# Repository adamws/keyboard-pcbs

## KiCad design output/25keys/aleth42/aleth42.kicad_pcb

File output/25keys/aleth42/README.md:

## 25keys/aleth42

[layout](aleth42-kle.json) - [PCB](aleth42.kicad_pcb)

{:loading="lazy"}

[Open in keyboard-layout-editor](http://www.keyboard-layout-editor.com/##@@_c=#777777;&=0,0&_c=#cccccc;&=0,1&=0,2&=0,3&=0,4&=0,5&=0,6&=0,7&=0,8&=0,9&=0,10&_c=#aaaaaa;&=3,10;&@_w:1.25;&=1,0&_c=#cccccc;&=1,1&=1,2&=1,3&=1,4&=1,5&=1,6&=1,7&=1,8&=1,9&_c=#777777&w:1.75;&=1,10;&@_c=#aaaaaa&w:1.75;&=2,0&_c=#cccccc;&=2,1&=2,2&=2,3&=2,4&=2,5&=2,6&=2,7&=2,8&=2,9&_c=#aaaaaa&w:1.25;&=2,10;&@=3,0&_w:1.25;&=3,1&_w:1.25;&=3,2&_w:2.75;&=3,3&_w:2.25;&=3,4&_w:1.25;&=3,5&_w:1.25;&=3,6&=3,7)

{:loading="lazy"}

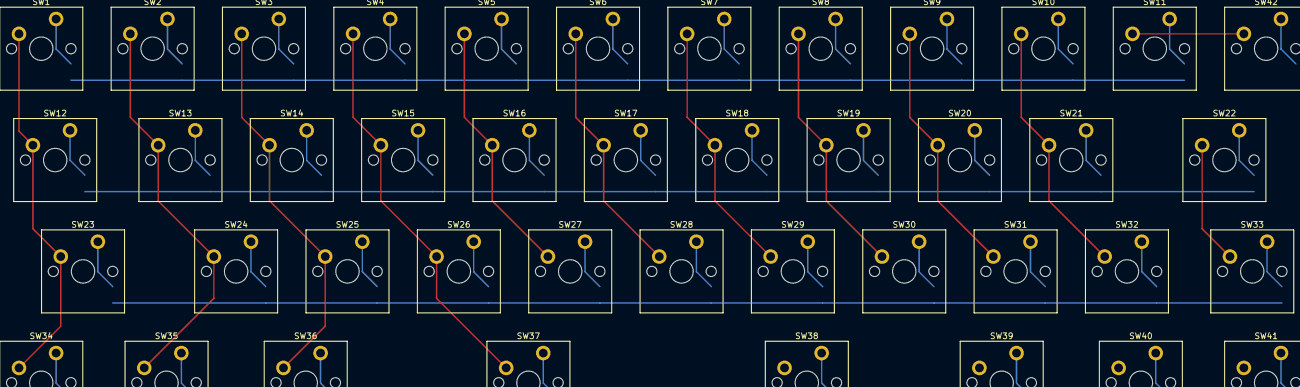
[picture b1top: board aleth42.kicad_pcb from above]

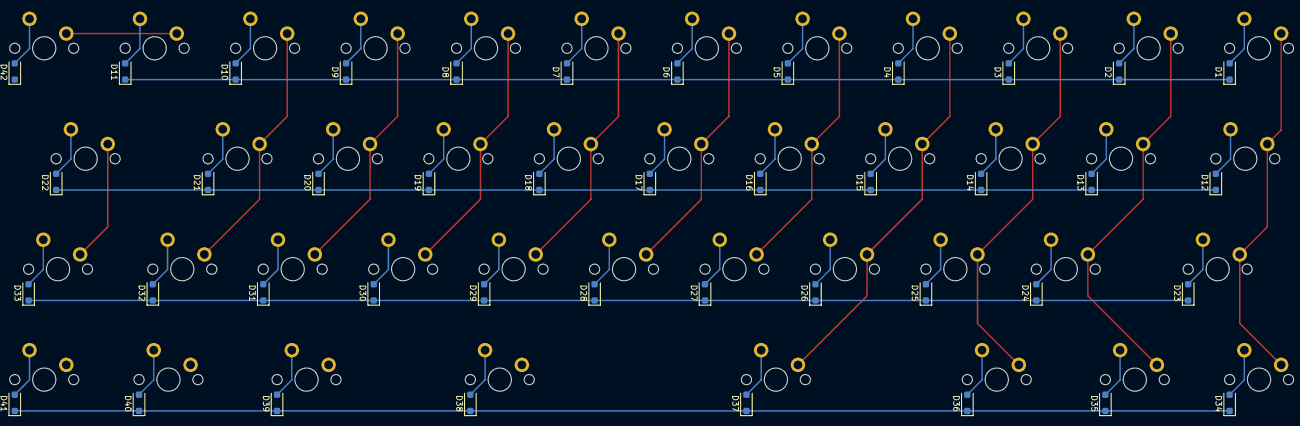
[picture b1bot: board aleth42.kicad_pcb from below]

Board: 2 copper layers, 84 parts (42 on the bottom side), 57 nets.

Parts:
D1, D2, D3, D4, D5, D6, D7, D8, D9, D10, D11, D12, D13, D14, D15, D16, D17, D18, D19, D20, D21, D22, D23, D24, D25, D26, D27, D28, D29, D30, D31, D32, D33, D34, D35, D36, D37, D38, D39, D40, D41, D42: D_SOD-123F
SW1, SW2, SW3, SW4, SW5, SW6, SW7, SW8, SW9, SW10, SW11, SW12, SW13, SW14, SW15, SW16, SW17, SW18, SW19, SW20, SW21, SW22, SW23, SW24, SW25, SW26, SW27, SW28, SW29, SW30, SW31, SW32, SW33, SW34, SW35, SW36, SW37, SW38, SW39, SW40, SW41, SW42: SW_Cherry_MX_PCB_1.00u

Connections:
COL0: SW1.1, SW12.1, SW23.1, SW34.1
COL1: SW2.1, SW13.1, SW24.1, SW35.1
COL2: SW3.1, SW14.1, SW25.1, SW36.1
COL3: SW4.1, SW15.1, SW26.1, SW37.1
COL4: SW5.1, SW16.1, SW27.1, SW38.1
COL5: SW6.1, SW17.1, SW28.1, SW39.1
COL6: SW7.1, SW18.1, SW29.1, SW40.1
COL7: SW8.1, SW19.1, SW30.1, SW41.1
COL8: SW9.1, SW20.1, SW31.1
COL9: SW10.1, SW21.1, SW32.1
COL10: SW11.1, SW22.1, SW33.1, SW42.1
unnamed: D1.2, SW1.2
unnamed: D2.2, SW2.2
unnamed: D3.2, SW3.2
unnamed: D4.2, SW4.2
unnamed: D5.2, SW5.2
unnamed: D6.2, SW6.2
unnamed: D7.2, SW7.2
unnamed: D8.2, SW8.2
unnamed: D9.2, SW9.2
unnamed: D10.2, SW10.2
unnamed: D11.2, SW11.2
unnamed: D12.2, SW12.2
unnamed: D13.2, SW13.2
unnamed: D14.2, SW14.2
unnamed: D15.2, SW15.2
unnamed: D16.2, SW16.2
unnamed: D17.2, SW17.2
unnamed: D18.2, SW18.2
unnamed: D19.2, SW19.2
unnamed: D20.2, SW20.2
unnamed: D21.2, SW21.2
unnamed: D22.2, SW22.2
unnamed: D23.2, SW23.2
unnamed: D24.2, SW24.2
unnamed: D25.2, SW25.2
unnamed: D26.2, SW26.2
unnamed: D27.2, SW27.2
unnamed: D28.2, SW28.2
unnamed: D29.2, SW29.2
unnamed: D30.2, SW30.2
unnamed: D31.2, SW31.2
unnamed: D32.2, SW32.2
unnamed: D33.2, SW33.2
unnamed: D34.2, SW34.2
unnamed: D35.2, SW35.2
unnamed: D36.2, SW36.2
unnamed: D37.2, SW37.2
unnamed: D38.2, SW38.2
unnamed: D39.2, SW39.2
unnamed: D40.2, SW40.2
unnamed: D41.2, SW41.2
unnamed: D42.2, SW42.2
ROW0: D1.1, D2.1, D3.1, D4.1, D5.1, D6.1, D7.1, D8.1, D9.1, D10.1, D11.1
ROW1: D12.1, D13.1, D14.1, D15.1, D16.1, D17.1, D18.1, D19.1, D20.1, D21.1, D22.1
ROW2: D23.1, D24.1, D25.1, D26.1, D27.1, D28.1, D29.1, D30.1, D31.1, D32.1, D33.1
ROW3: D34.1, D35.1, D36.1, D37.1, D38.1, D39.1, D40.1, D41.1, D42.1

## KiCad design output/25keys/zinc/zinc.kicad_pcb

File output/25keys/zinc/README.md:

## 25keys/zinc

[layout](zinc-kle.json) - [PCB](zinc.kicad_pcb)

{:loading="lazy"}

[Open in keyboard-layout-editor](http://www.keyboard-layout-editor.com/##@@_x:0.75&c=#aaaaaa;&=0,0%0A%0A%0A0,0&_c=#cccccc;&=0,1%0A%0A%0A0,0&=0,2%0A%0A%0A0,0&=0,3%0A%0A%0A0,0&=0,4%0A%0A%0A0,0&=0,5%0A%0A%0A0,0&_x:1.75;&=4,0&=4,1&=4,2&=4,3&=4,4&_c=#aaaaaa;&=4,5;&@_x:1;&=1,0%0A%0A%0A0,0&_c=#cccccc;&=1,1%0A%0A%0A0,0&=1,2%0A%0A%0A0,0&=1,3%0A%0A%0A0,0&=1,4%0A%0A%0A0,0&=1,5%0A%0A%0A0,0&_x:1.75;&=5,0&=5,1&=5,2&=5,3&=5,4&=5,5;&@_x:1.25&c=#aaaaaa;&=2,0%0A%0A%0A0,0&_c=#cccccc;&=2,1%0A%0A%0A0,0&=2,2%0A%0A%0A0,0&=2,3%0A%0A%0A0,0&=2,4%0A%0A%0A0,0&=2,5%0A%0A%0A0,0&_x:1.75;&=6,0&=6,1&=6,2&=6,3&=6,4&_c=#aaaaaa;&=6,5;&@_x:1.5;&=3,0%0A%0A%0A0,0&=3,1%0A%0A%0A0,0&=3,2%0A%0A%0A0,0&=3,3%0A%0A%0A0,0&=3,4%0A%0A%0A0,0&_c=#cccccc;&=3,5%0A%0A%0A0,0&_x:1.75;&=7,0&_c=#aaaaaa;&=7,1&=7,2&=7,3&=7,4&=7,5;&@_x:2.25&y:0.5;&=0,0%0A%0A%0A0,1&_c=#cccccc;&=0,1%0A%0A%0A0,1&=0,2%0A%0A%0A0,1&=0,3%0A%0A%0A0,1&=0,4%0A%0A%0A0,1&=0,5%0A%0A%0A0,1;&@_x:2&c=#aaaaaa;&=1,0%0A%0A%0A0,1&_c=#cccccc;&=1,1%0A%0A%0A0,1&=1,2%0A%0A%0A0,1&=1,3%0A%0A%0A0,1&=1,4%0A%0A%0A0,1&=1,5%0A%0A%0A0,1;&@_x:1.75&c=#aaaaaa;&=2,0%0A%0A%0A0,1&_c=#cccccc;&=2,1%0A%0A%0A0,1&=2,2%0A%0A%0A0,1&=2,3%0A%0A%0A0,1&=2,4%0A%0A%0A0,1&=2,5%0A%0A%0A0,1;&@_x:1.5&c=#aaaaaa;&=3,0%0A%0A%0A0,1&=3,1%0A%0A%0A0,1&=3,2%0A%0A%0A0,1&=3,3%0A%0A%0A0,1&=3,4%0A%0A%0A0,1&_c=#cccccc;&=3,5%0A%0A%0A0,1)

{:loading="lazy"}

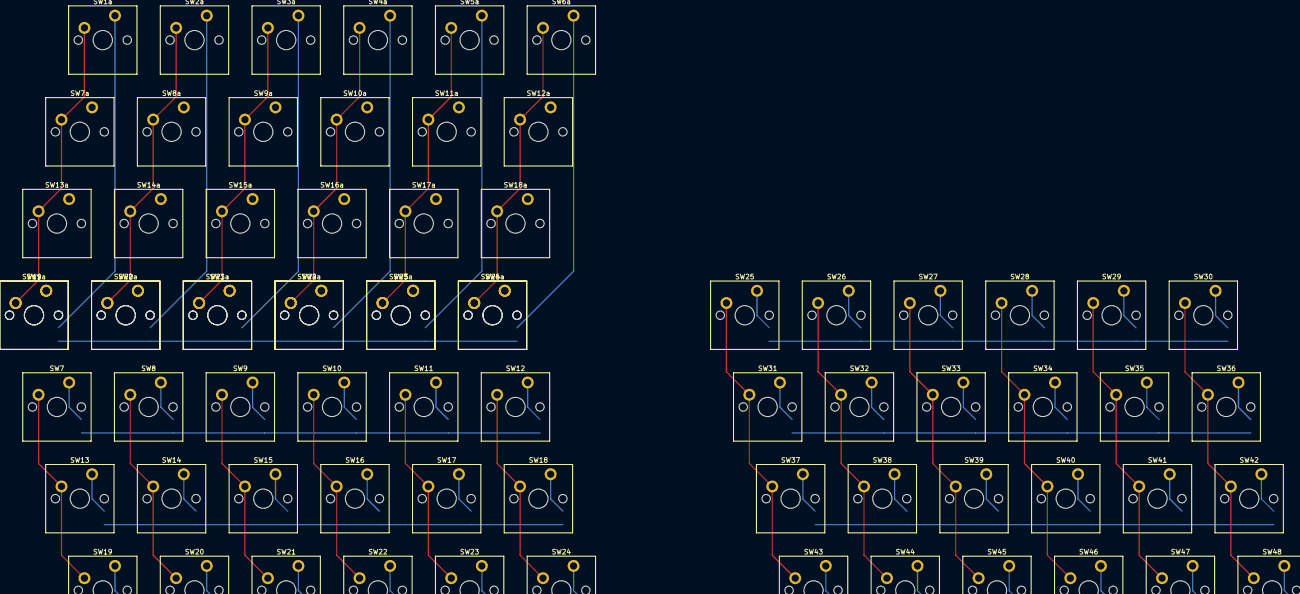
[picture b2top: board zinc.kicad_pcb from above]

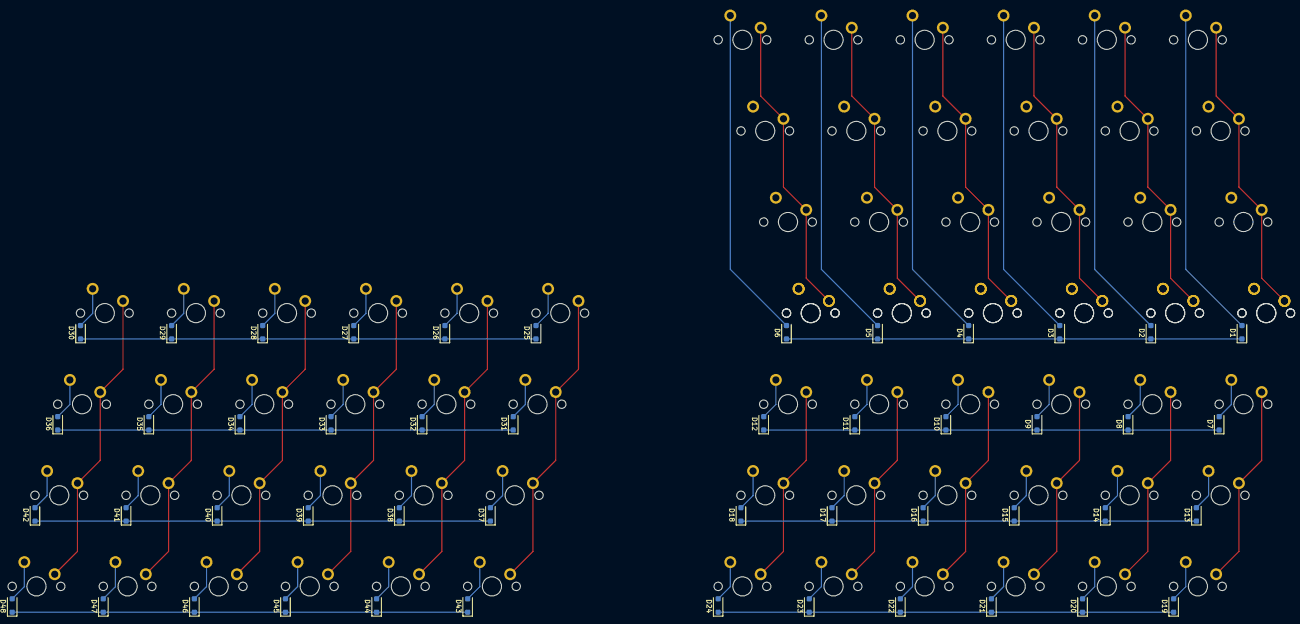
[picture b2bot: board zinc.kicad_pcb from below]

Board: 2 copper layers, 120 parts (48 on the bottom side), 62 nets.

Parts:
D1, D2, D3, D4, D5, D6, D7, D8, D9, D10, D11, D12, D13, D14, D15, D16, D17, D18, D19, D20, D21, D22, D23, D24, D25, D26, D27, D28, D29, D30, D31, D32, D33, D34, D35, D36, D37, D38, D39, D40, D41, D42, D43, D44, D45, D46, D47, D48: D_SOD-123F
SW1, SW1a, SW2, SW2a, SW3, SW3a, SW4, SW4a, SW5, SW5a, SW6, SW6a, SW7, SW7a, SW8, SW8a, SW9, SW9a, SW10, SW10a, SW11, SW11a, SW12, SW12a, SW13, SW13a, SW14, SW14a, SW15, SW15a, SW16, SW16a, SW17, SW17a, SW18, SW18a, SW19, SW19a, SW20, SW20a, SW21, SW21a, SW22, SW22a, SW23, SW23a, SW24, SW24a, SW25, SW26, SW27, SW28, SW29, SW30, SW31, SW32, SW33, SW34, SW35, SW36, SW37, SW38, SW39, SW40, SW41, SW42, SW43, SW44, SW45, SW46, SW47, SW48: SW_Cherry_MX_PCB_1.00u

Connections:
COL0: SW1.1, SW1a.1, SW7.1, SW7a.1, SW13.1, SW13a.1, SW19.1, SW19a.1, SW25.1, SW31.1, SW37.1, SW43.1
COL1: SW2.1, SW2a.1, SW8.1, SW8a.1, SW14.1, SW14a.1, SW20.1, SW20a.1, SW26.1, SW32.1, SW38.1, SW44.1
COL2: SW3.1, SW3a.1, SW9.1, SW9a.1, SW15.1, SW15a.1, SW21.1, SW21a.1, SW27.1, SW33.1, SW39.1, SW45.1
COL3: SW4.1, SW4a.1, SW10.1, SW10a.1, SW16.1, SW16a.1, SW22.1, SW22a.1, SW28.1, SW34.1, SW40.1, SW46.1
COL4: SW5.1, SW5a.1, SW11.1, SW11a.1, SW17.1, SW17a.1, SW23.1, SW23a.1, SW29.1, SW35.1, SW41.1, SW47.1
COL5: SW6.1, SW6a.1, SW12.1, SW12a.1, SW18.1, SW18a.1, SW24.1, SW24a.1, SW30.1, SW36.1, SW42.1, SW48.1
unnamed: D1.2, SW1.2, SW1a.2
unnamed: D2.2, SW2.2, SW2a.2
unnamed: D3.2, SW3.2, SW3a.2
unnamed: D4.2, SW4.2, SW4a.2
unnamed: D5.2, SW5.2, SW5a.2
unnamed: D6.2, SW6.2, SW6a.2
unnamed: D7.2, SW7.2, SW7a.2
unnamed: D8.2, SW8.2, SW8a.2
unnamed: D9.2, SW9.2, SW9a.2
unnamed: D10.2, SW10.2, SW10a.2
unnamed: D11.2, SW11.2, SW11a.2
unnamed: D12.2, SW12.2, SW12a.2
unnamed: D13.2, SW13.2, SW13a.2
unnamed: D14.2, SW14.2, SW14a.2
unnamed: D15.2, SW15.2, SW15a.2
unnamed: D16.2, SW16.2, SW16a.2
unnamed: D17.2, SW17.2, SW17a.2
unnamed: D18.2, SW18.2, SW18a.2
unnamed: D19.2, SW19.2, SW19a.2
unnamed: D20.2, SW20.2, SW20a.2
unnamed: D21.2, SW21.2, SW21a.2
unnamed: D22.2, SW22.2, SW22a.2
unnamed: D23.2, SW23.2, SW23a.2
unnamed: D24.2, SW24.2, SW24a.2
unnamed: D25.2, SW25.2
unnamed: D26.2, SW26.2
unnamed: D27.2, SW27.2
unnamed: D28.2, SW28.2
unnamed: D29.2, SW29.2
unnamed: D30.2, SW30.2
unnamed: D31.2, SW31.2
unnamed: D32.2, SW32.2
unnamed: D33.2, SW33.2
unnamed: D34.2, SW34.2
unnamed: D35.2, SW35.2
unnamed: D36.2, SW36.2
unnamed: D37.2, SW37.2
unnamed: D38.2, SW38.2
unnamed: D39.2, SW39.2
unnamed: D40.2, SW40.2
unnamed: D41.2, SW41.2
unnamed: D42.2, SW42.2
unnamed: D43.2, SW43.2
unnamed: D44.2, SW44.2
unnamed: D45.2, SW45.2
unnamed: D46.2, SW46.2
unnamed: D47.2, SW47.2
unnamed: D48.2, SW48.2
ROW0: D1.1, D2.1, D3.1, D4.1, D5.1, D6.1
ROW1: D7.1, D8.1, D9.1, D10.1, D11.1, D12.1
ROW2: D13.1, D14.1, D15.1, D16.1, D17.1, D18.1
ROW3: D19.1, D20.1, D21.1, D22.1, D23.1, D24.1
ROW4: D25.1, D26.1, D27.1, D28.1, D29.1, D30.1
ROW5: D31.1, D32.1, D33.1, D34.1, D35.1, D36.1
ROW6: D37.1, D38.1, D39.1, D40.1, D41.1, D42.1
ROW7: D43.1, D44.1, D45.1, D46.1, D47.1, D48.1
